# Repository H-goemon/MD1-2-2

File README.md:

# MD1-2-2

MD1-2を改良したもの。

サイズが小さくなった。

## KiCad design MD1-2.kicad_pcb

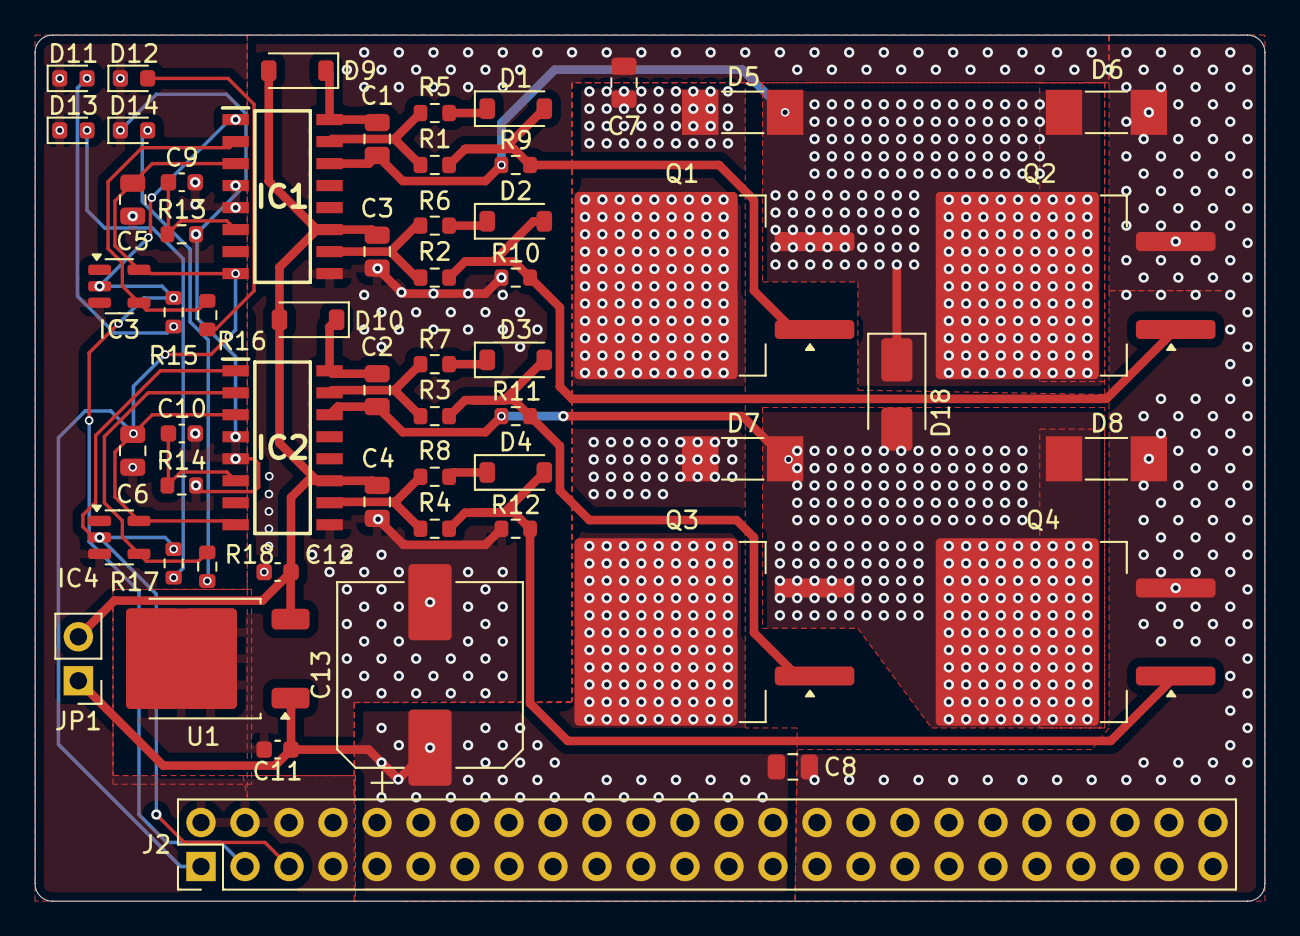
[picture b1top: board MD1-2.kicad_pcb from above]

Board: 2 copper layers, 71.0 x 50.0 mm, 57 parts (0 on the bottom side), 31 nets.

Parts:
C1, C2, C5, C6, C7, C8: 10μF; C_0805_2012Metric
C3, C4: C; C_0805_2012Metric
C9: 2.2nF; C_0603_1608Metric
C10: C; C_0603_1608Metric
C11: 0.33μF; C_0603_1608Metric
C12: 0.1μF; C_0603_1608Metric
C13: 47μF; CP_Elec_10x10.5
D1, D2, D3, D4, D9, D10: 1N4148W; D_SOD-123
D5, D6, D7, D8: D; R_MELF_MMB-0207
D11, D12, D13, D14: LED; LED_0603_1608Metric
D18: SMAJ30CA; D_SMA
IC1, IC2: UCC21330BDR; SOIC127P600X175-16N
IC3, IC4: TC7S14F; SOT-23-5
J2: メイン接続端子; PinHeader_2x24_P2.54mm_Vertical
JP1: 24V⇔12V切り替え; PinHeader_1x02_P2.54mm_Vertical
Q1, Q2, Q3, Q4: NMOS; TO-263-2
R1, R2, R3, R4, R5, R6, R7, R8: 10Ω; R_0603_1608Metric
R9, R10, R11, R12: 10kΩ; R_0603_1608Metric
R13, R14: R; R_0603_1608Metric
R15, R16, R17, R18: 1kΩ; R_0603_1608Metric
U1: L7812; TO-252-2

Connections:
+3.3V: C5.1, C6.1, IC1.3 (VCCI_1), IC1.8 (VCCI_2), IC2.3 (VCCI_1), IC2.8 (VCCI_2), IC3.5 (VCC), IC4.5 (VCC), J2.1
+12V: C3.1, C4.1, C12.1, D9.2 (A), D10.2 (A), IC1.11 (VDDB), IC2.11 (VDDB), JP1.2 (B), U1.3 (OUT)
+BATT: C7.1, C8.1, C11.1, C13.1, D5.1 (K), D7.1 (K), J2.9, J2.10, J2.11, J2.12, J2.13, J2.14, J2.15, J2.16, J2.17, J2.18, J2.19, J2.20, J2.21, J2.22, J2.23, J2.24, J2.25, J2.26, J2.27, J2.28, JP1.1 (A), Q1.1 (D), Q3.1 (D), U1.1 (IN)
/L-OUT: C2.2, D7.2 (A), D8.1 (K), D18.2 (A2), IC2.14 (VSSA), Q3.3 (S), Q4.1 (D), R11.2
/LDT-set: C10.1, IC2.6 (DT), R14.1
/LHi-Out: IC2.15 (OUTA), R3.1, R7.1
/LHi-sig: IC2.1 (INA), IC4.2 (IN_A), J2.5, R17.1
/LLo-Out: IC2.10 (OUTB), R4.1, R8.1
/LLo-sig: IC2.2 (INB), IC4.4 (OUT_Y), R18.1
/R-OUT: C1.2, D5.2 (A), D6.1 (K), D18.1 (A1), IC1.14 (VSSA), Q1.3 (S), Q2.1 (D), R9.1
/RDT-set: C9.1, IC1.6 (DT), R13.1
/RHi-Out: IC1.15 (OUTA), R1.1, R5.1
/RHi-sig: IC1.1 (INA), IC3.2 (IN_A), J2.3, R15.1
/RLo-Out: IC1.10 (OUTB), R2.1, R6.1
/RLo-sig: IC1.2 (INB), IC3.4 (OUT_Y), R16.1
GND: C5.2, C6.2, C9.2, C10.2, D11.1 (K), D12.1 (K), D13.1 (K), D14.1 (K), IC1.4 (GND), IC1.5 (DIS), IC2.4 (GND), IC2.5 (DIS), IC3.3 (GND), IC4.3 (GND), J2.2, J2.4, J2.6, J2.7, J2.8, R13.2, R14.2
GNDPWR: C3.2, C4.2, C7.2, C8.2, C11.2, C12.2, C13.2, D6.2 (A), D8.2 (A), IC1.9 (VSSB), IC2.9 (VSSB), J2.29, J2.30, J2.31, J2.32, J2.33, J2.34, J2.35, J2.36, J2.37, J2.38, J2.39, J2.40, J2.41, J2.42, J2.43, J2.44, J2.45, J2.46, J2.47, J2.48, Q2.3 (S), Q4.3 (S), R10.2, R12.2, U1.2 (GND)
unnamed: D1.2 (A), Q1.2 (G), R1.2, R9.2
unnamed: D1.1 (K), R5.2
unnamed: D2.2 (A), Q2.2 (G), R2.2, R10.1
unnamed: D2.1 (K), R6.2
unnamed: D3.2 (A), Q3.2 (G), R3.2, R11.1
unnamed: D3.1 (K), R7.2
unnamed: D4.2 (A), Q4.2 (G), R4.2, R12.1
unnamed: D4.1 (K), R8.2
unnamed: C1.1, D9.1 (K), IC1.16 (VDDA)
unnamed: C2.1, D10.1 (K), IC2.16 (VDDA)
unnamed: D11.2 (A), R15.2
unnamed: D12.2 (A), R16.2
unnamed: D13.2 (A), R17.2
unnamed: D14.2 (A), R18.2
